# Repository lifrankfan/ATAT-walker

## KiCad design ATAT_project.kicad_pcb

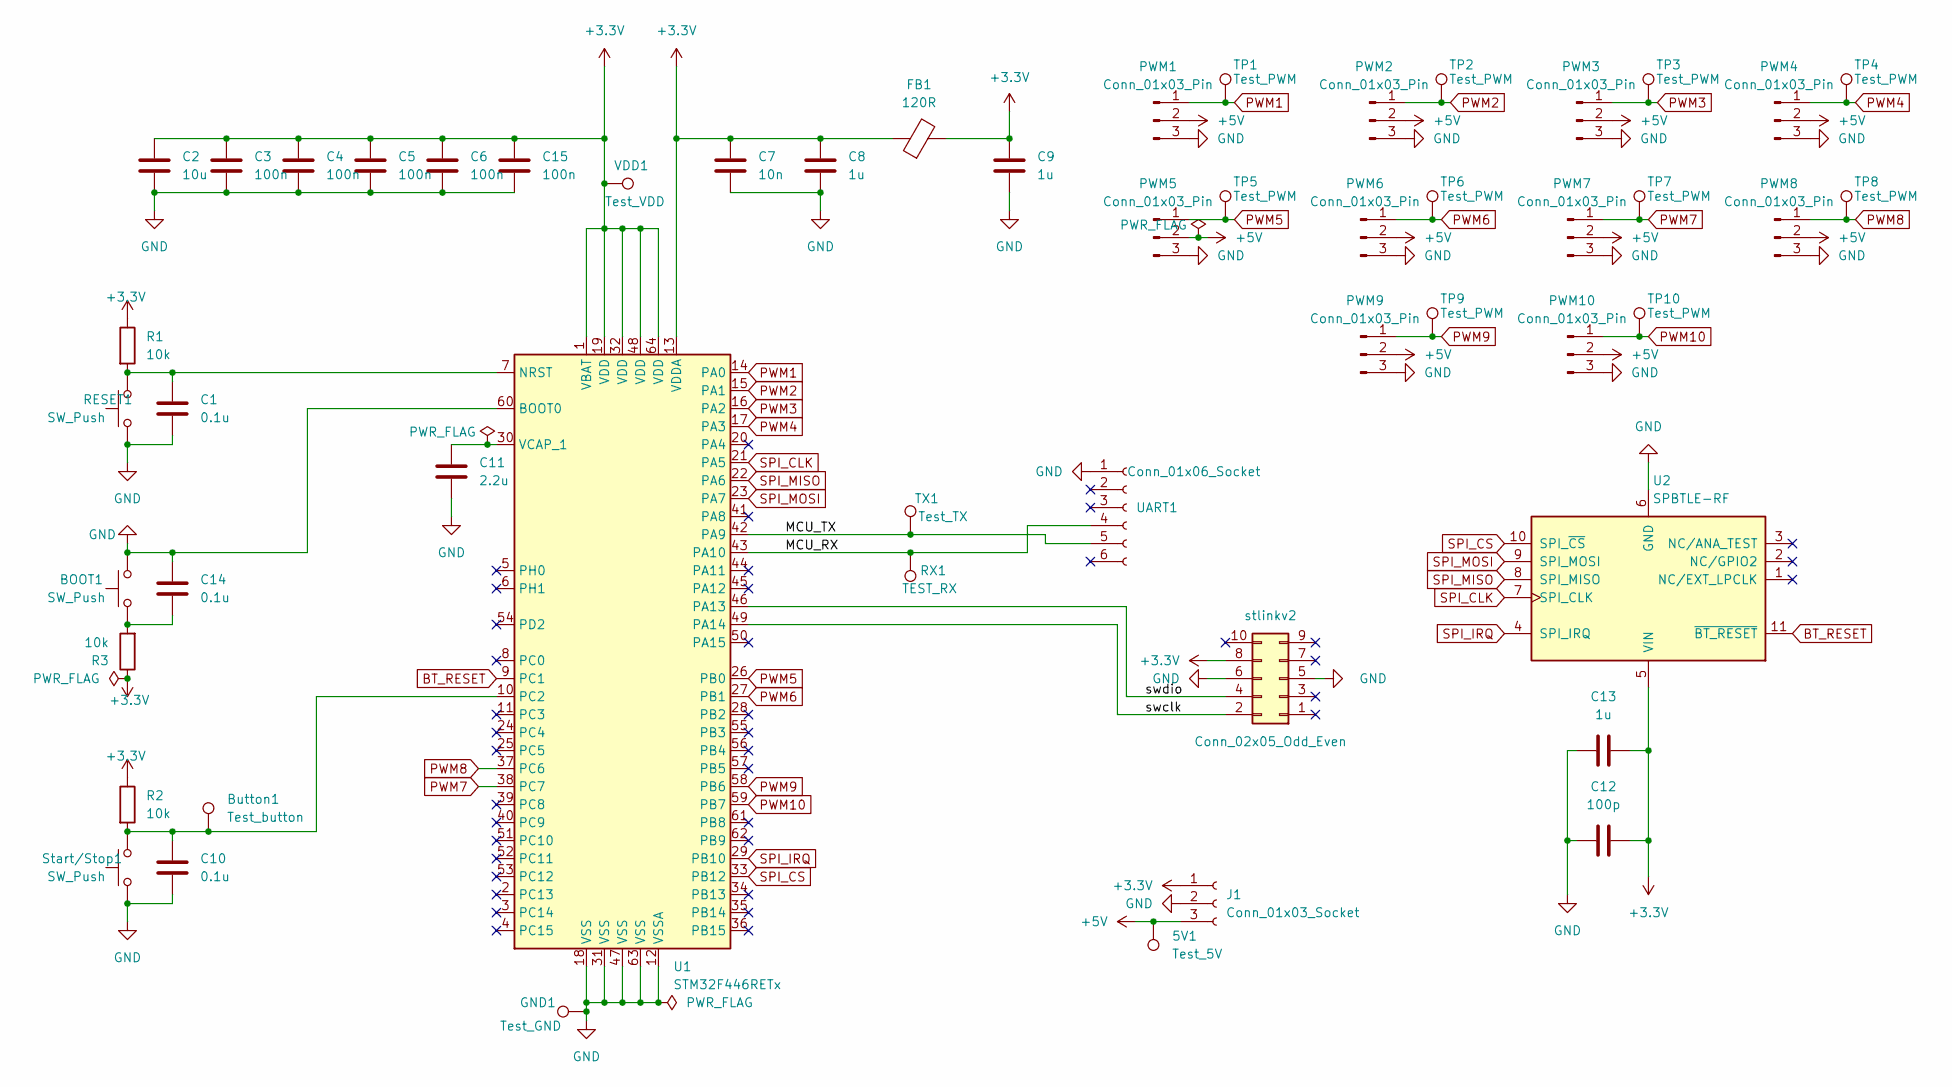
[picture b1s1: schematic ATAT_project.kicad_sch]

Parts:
5V1: Test_5V; TestPoint_Pad_D1.0mm
BOOT1: SW_Push; SW_PUSH_6mm_H4.3mm
Button1: Test_button; TestPoint_Pad_D1.0mm
C1, C10, C14: 0.1u; C_0805_2012Metric_Pad1.18x1.45mm_HandSolder
C2: 10u; C_0805_2012Metric_Pad1.18x1.45mm_HandSolder
C3, C4, C5, C6, C15: 100n; C_0805_2012Metric_Pad1.18x1.45mm_HandSolder
C7: 10n; C_0805_2012Metric_Pad1.18x1.45mm_HandSolder
C8, C9, C13: 1u; C_0805_2012Metric_Pad1.18x1.45mm_HandSolder
C11: 2.2u; C_0805_2012Metric_Pad1.18x1.45mm_HandSolder
C12: 100p; C_0805_2012Metric_Pad1.18x1.45mm_HandSolder
FB1: 120R; R_0805_2012Metric_Pad1.20x1.40mm_HandSolder
GND1: Test_GND; TestPoint_Pad_D1.0mm
J1: Conn_01x03_Socket; PinSocket_1x03_P2.54mm_Vertical
PWM1, PWM2, PWM3, PWM4, PWM5, PWM6, PWM7, PWM8, PWM9, PWM10: Conn_01x03_Pin; PinHeader_1x03_P2.54mm_Vertical
R1, R2, R3: 10k; R_0805_2012Metric_Pad1.20x1.40mm_HandSolder
RESET1: SW_Push; SW_PUSH_6mm_H4.3mm
RX1: TEST_RX; TestPoint_Pad_D1.0mm
Start/Stop1: SW_Push; SW_PUSH_6mm_H4.3mm
TP1, TP2, TP3, TP4, TP5, TP6, TP7, TP8, TP9, TP10: Test_PWM; TestPoint_Pad_D1.0mm
TX1: Test_TX; TestPoint_Pad_D1.0mm
U1: STM32F446RETx; LQFP-64_10x10mm_P0.5mm
U2: SPBTLE-RF; ST_SPBTLE
UART1: Conn_01x06_Socket; PinSocket_1x06_P2.54mm_Vertical
VDD1: Test_VDD; TestPoint_Pad_D1.0mm
stlinkv2: Conn_02x05_Odd_Even; PinHeader_2x05_P2.54mm_Vertical

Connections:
+3.3V: C2.1, C3.1, C4.1, C5.1, C6.1, C7.1, C8.1, C9.1, C12.2, C13.2, C15.1, FB1.1, FB1.2, J1.1, R1.1, R2.1, R3.1, U1.1 (VBAT), U1.13 (VDDA), U1.19 (VDD), U1.32 (VDD), U1.48 (VDD), U1.64 (VDD), U2.5 (VIN), VDD1.1, stlinkv2.8
+5V: 5V1.1, J1.3, PWM1.2, PWM2.2, PWM3.2, PWM4.2, PWM5.2, PWM6.2, PWM7.2, PWM8.2, PWM9.2, PWM10.2
/MCU_RX: RX1.1, U1.43 (PA10), UART1.4
/MCU_TX: TX1.1, U1.42 (PA9), UART1.5
/swclk: U1.49 (PA14), stlinkv2.2
/swdio: U1.46 (PA13), stlinkv2.4
BT_RESET: U1.9 (PC1), U2.11 (~BT_RESET)
GND: BOOT1.2, C1.2, C2.2, C3.2, C4.2, C5.2, C6.2, C7.2, C8.2, C9.2, C10.2, C11.2, C12.1, C13.1, C14.1, C15.2, GND1.1, J1.2, PWM1.3, PWM2.3, PWM3.3, PWM4.3, PWM5.3, PWM6.3, PWM7.3, PWM8.3, PWM9.3, PWM10.3, RESET1.1, Start/Stop1.1, U1.12 (VSSA), U1.18 (VSS), U1.31 (VSS), U1.47 (VSS), U1.60 (BOOT0), U1.63 (VSS), U2.6 (GND), UART1.1, stlinkv2.5, stlinkv2.6
unnamed: BOOT1.1, C14.2, R3.2
unnamed: C1.1, R1.2, RESET1.2, U1.7 (NRST)
unnamed: Button1.1, C10.1, R2.2, Start/Stop1.2, U1.10 (PC2)
unnamed: C11.1, U1.30 (VCAP_1)
PWM1: PWM1.1, TP1.1, U1.14 (PA0)
PWM2: PWM2.1, TP2.1, U1.15 (PA1)
PWM3: PWM3.1, TP3.1, U1.16 (PA2)
PWM4: PWM4.1, TP4.1, U1.17 (PA3)
PWM5: PWM5.1, TP5.1, U1.26 (PB0)
PWM6: PWM6.1, TP6.1, U1.27 (PB1)
PWM7: PWM7.1, TP7.1, U1.38 (PC7)
PWM8: PWM8.1, TP8.1, U1.37 (PC6)
PWM9: PWM9.1, TP9.1, U1.58 (PB6)
PWM10: PWM10.1, TP10.1, U1.59 (PB7)
SPI_CLK: U1.21 (PA5), U2.7 (SPI_CLK)
SPI_CS: U1.33 (PB12), U2.10 (SPI_~CS)
SPI_IRQ: U1.29 (PB10), U2.4 (SPI_IRQ)
SPI_MISO: U1.22 (PA6), U2.8 (SPI_MISO)
SPI_MOSI: U1.23 (PA7), U2.9 (SPI_MOSI)

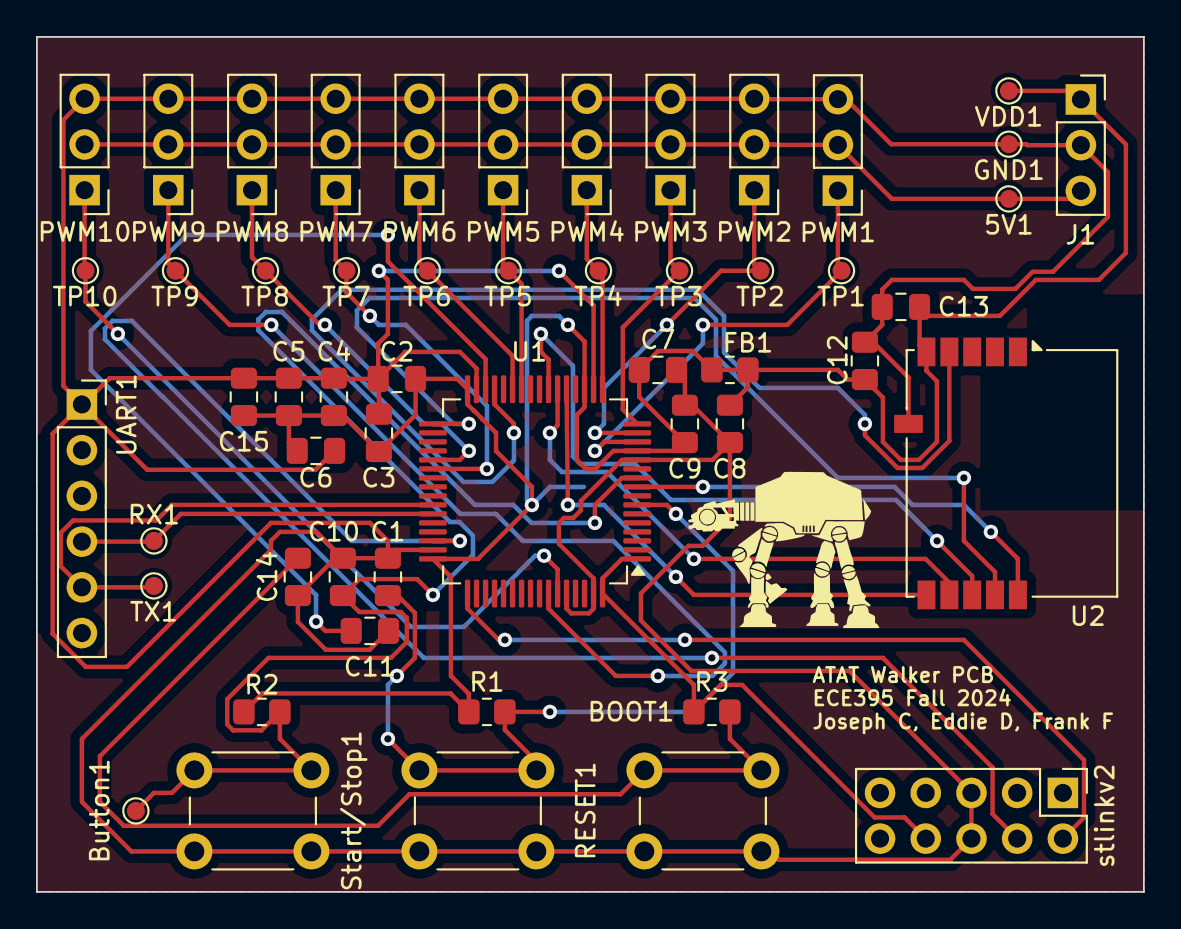
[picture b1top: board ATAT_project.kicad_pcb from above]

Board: 2 copper layers, 61.5 x 47.5 mm, 53 parts (0 on the bottom side), 27 nets.

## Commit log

2024-11-02 Updated Schematic
2024-11-03 Added footprints
2024-11-03 basic pcb layout
2024-11-03 scuffed but done
2024-11-04 Fixed all DRC, started Casey's feedback
2024-11-08 NEW SCHEMATIC! (Needs PCB Design)
2024-11-08 NEW PCB!!!
